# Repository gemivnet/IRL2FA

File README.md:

# IRL2FA

**An air-gapped key fob that proves the person on the other end is who they say they are, and keeps your 2FA codes off your phone.**

AI can now clone a voice from a few seconds of audio and write messages in anyone's style. "It's me, I lost my phone, can you send…" is no longer something you can judge by ear. IRL2FA gives two people a shared secret they set up **once, in person**. From then on, each device shows two words that change every 15 seconds: the word you **say** and the word you should **hear** back. If the reply matches, the other person is holding the device you paired with face to face.

It is also a standard **TOTP authenticator** (the 6-digit codes from Google Authenticator and similar apps) for up to 512 accounts. It has no USB data port, no radio and no network. The only control is a 5-way joystick.

<p align="center">
  <a href="https://irl2fa.com/"><b>▶ Try it in your browser</b></a> ·
  <a href="#build-one">Build one</a> ·
  <a href="docs/pairing-protocol.md">How pairing works</a> ·
  <a href="https://github.com/gemivnet/IRL2FA/releases/latest">Download</a>
</p>

---

## How it works

**Pair once, in person.**

1. Both people choose *Pair with someone* and hold their devices top edge to top edge.
2. The devices agree a 256-bit key over infrared using X25519, with a commitment scheme that stops a man in the middle.
3. Both screens show the same six joystick symbols. You compare them, confirm, and name the contact.

**Verify any time after.**

- Open the contact. Say the **SAY** word; they should answer with your **HEAR** word.
- Words come from HMAC-SHA256 over the current 15-second window, mapped onto the 2048-word BIP-39 list.
- Nothing is ever transmitted again, so there is nothing to intercept.

**TOTP codes.**

- Add an account by typing the base32 secret most sites show under "can't scan the QR code?".
- RFC 6238; SHA1/SHA256/SHA512; 6 or 8 digits; 30 or 60 s.

**Secrets at rest.**

- Every record, labels included, is sealed with XChaCha20-Poly1305 in the MCU's read-protected flash.
- An optional joystick PIN wraps the key with Argon2i. Ten wrong PINs erase the device.

The full design is in [docs/pairing-protocol.md](docs/pairing-protocol.md) and [docs/ui-flows.md](docs/ui-flows.md).

## For family members

Setting one up for a parent, grandparent or child who should only check who is calling? Use **simple mode** (the docs call it vulnerable mode). The device then shows one thing: the name of the person, and in big letters the word that person will say. "If they don't say this word, hang up and call them back." Up and down go to the next person. Nothing else does anything: no menus, no codes, no settings.

1. Pair the device in person with everyone who might call, and give each contact a name they will recognise ("Susan", "Grandpa Joe").
2. **Settings → Simple mode**, then choose a **family PIN** of 6 or more joystick moves and enter it three times. Write it down: it cannot be reset.
3. Give them the device. When you call, open their contact on your own device and say your **SAY** word.

To change anything later, hold the centre of the joystick for 10 seconds and enter the family PIN. Wrong family PINs never erase the device; they make the next try wait longer, up to an hour. Details and the security trade-offs are in [docs/ui-flows.md](docs/ui-flows.md#vulnerable-simple-mode).

## Try the simulator

The firmware's portable core is compiled to WebAssembly and runs two devices side by side in your browser: pair them over a simulated IR link, compare words, add a TOTP secret and check it against your phone.

It behaves like the hardware, not just like the firmware:

- **E-paper.** A full refresh flashes black and white for 3 s; a partial one takes 0.42 s and leaves faint ghosting that builds up until the firmware's next full refresh. Presses during a refresh are queued, as on the board.
- **IR link.** Set the distance and angle between the devices. Bit errors and dropouts rise with distance, and bytes take their real airtime at 4800 baud on a half-duplex link; the firmware listens before it talks. Beyond about 9 cm pairing keeps retrying and gives up after a minute.
- **Battery.** The panel uses the same power model as the [battery budget](docs/power-calculations.md), generated from `hardware/power`. Fast-forward days or years of use and watch the remaining life and the cell voltage fall.

**[irl2fa.com](https://irl2fa.com/)**

## Hardware

| | |
|-|-|
| MCU | STM32U083KCU6: Cortex-M0+, 256 KB flash, 40 KB RAM, TRNG, readout protection |
| Display | 2.13″ e-paper, 250×122, Good Display GDEY0213B74 (SSD1680) |
| Clock | Micro Crystal RV-3032-C7, temperature-compensated ±2.5 ppm |
| Input | Alps SKRHABE010 5-way switch, the only control |
| Pairing | 940 nm side-looking IR LED and phototransistor on the top edge |
| Power | CR2450 coin cell. **About 2.8 years typical, 1.6 years worst case** at 20 uses a day, with the awake time and refreshes measured on the emulated firmware ([calculation](docs/power-calculations.md)) |
| Board | 77 × 31 mm, 2 layers, 0.8 mm, ENIG. JLCPCB can assemble every part except the display |
| Case | 80.9 × 34.9 × 11.0 mm, 3D-printed in 4 parts, M2 screws |

- Design files: [schematic (PDF)](hardware/fab/irl2fa-schematic.pdf) · [KiCad 9 project](hardware/) · [interactive BOM](https://irl2fa.com/ibom.html) · [3D model (STEP)](hardware/fab/irl2fa.step)
- Design notes: [PCB design](docs/pcb-design.md) · [pin assignments](docs/pin-assignments.md) · [why these parts](docs/hardware-options.md) · [design review](docs/design-review.md) · [firmware against the silicon](docs/firmware-hardware-review.md)

## Build one

You need a PCB, a display, a coin cell, a printed case and four screws. Everything to order is committed and kept current by CI.

1. **Order the assembled board** from [JLCPCB](https://jlcpcb.com). The form has a few answers that would spoil the boards; [docs/assembly-review.md](docs/assembly-review.md#ordering-at-jlcpcb) explains each one.
   - Upload [`hardware/fab/irl2fa-gerbers.zip`](hardware/fab/irl2fa-gerbers.zip) and keep the detected size (77 × 31 mm) and 2 layers.
   - **Delivery format: Panel by JLCPCB**, 1 column × 2 rows, with **edge rails** on the long sides, joined by **stamp holes (mouse bites), not V-cut**. Assembling both sides needs Standard PCBA, which only takes boards or panels of at least 70 × 70 mm.
   - **PCB thickness 0.8 mm**, **surface finish ENIG** (a bare pad is the coin cell's negative contact), **via covering Tented**, 1 oz copper, any colour.
   - **Remove order number: Yes**: the board has no spot reserved for it.
   - Turn on **PCB Assembly**: **PCBA type Standard**, **assembly side Both sides** (the joystick is on the front, everything else on the back), **tooling holes added by JLCPCB**, **Confirm Parts Placement: Yes**.
   - Add [`irl2fa-bom-jlcpcb.csv`](hardware/fab/irl2fa-bom-jlcpcb.csv) and [`irl2fa-cpl-jlcpcb.csv`](hardware/fab/irl2fa-cpl-jlcpcb.csv). Every part has an LCSC number. The [BOM](docs/bill-of-materials.md) lists JLCPCB's stock, Basic/Extended parts and alternatives. The MCU and the RTC are often short, so check them before paying.
   - The placement file is already corrected for JLCPCB's own footprints. On the placement preview, check the polarised parts against the [expected-view table](docs/assembly-review.md#what-the-placement-preview-must-show), especially the IR LED and phototransistor (lenses at the top edge) and the coin-cell clip (open end at the bottom edge).
   - Paste the [order remark](docs/assembly-review.md#order-remark) into the remark box.
   - **Optional: have JLCPCB flash the firmware.** In the Standard PCBA options, open the advanced options and choose **programming**. JLCPCB asks for:
     - the MCU: **STM32U083KCU6**;
     - the programming interface: SWD on five test pads on the back, along the bottom edge, 1.5 mm round on a 2.54 mm grid: **TP2 GND, TP1 VBAT (supply 3.0 V), TP3 SWDIO, TP4 SWCLK, TP5 NRST**. Positions and a board image are in [docs/pcb-design.md](docs/pcb-design.md#factory-programming); attach [`docs/images/pcb/pcb-back.png`](docs/images/pcb/pcb-back.png);
     - the firmware: the factory image `irl2fa-factory-<version>.bin` from the [latest release](https://github.com/gemivnet/IRL2FA/releases) (bootloader + signed firmware in one file), written from the start of flash (0x08000000). Do not send the application's `.elf` alone: it does not start without the bootloader. The chip is left unprotected; readout protection is only ever turned on by its owner, from Settings.

     It costs about $8 in engineering fees plus operator time per board. JLCPCB decides per order whether it can program a part, so the option can be refused. A freshly programmed chip runs ST's bootloader, not the firmware, until it has seen a power-on reset ([firmware review](docs/firmware-hardware-review.md) F4): the board must be power-cycled after the first flash. Inserting the coin cell does that; a board that is checked still on the fixture after programming looks dead, and is not.
   - To solder it yourself, use the [interactive BOM](https://irl2fa.com/ibom.html).
2. **Buy the display.** A [Good Display GDEY0213B74](https://www.good-display.com/product/391.html) (about $5), or the GDEM0213B74WT if it has to work below 0 °C.
3. **Print the case.**
   - Files: [`case/stl/`](case/stl/) or [`case/3mf/irl2fa-all.3mf`](case/3mf/), in PETG or PLA with no supports.
   - Settings and assembly: [docs/case-design.md](docs/case-design.md).
4. **Flash the firmware.**
   - Get the factory image `irl2fa-factory-<version>.hex` (bootloader + signed firmware, for the whole chip) from the [latest release](https://github.com/gemivnet/IRL2FA/releases), or build `firmware/build/stm32u0/irl2fa-factory.hex` with `firmware/port/stm32u0/build.sh` (unsigned: a development unit).
   - Flash it through a Tag-Connect TC2030-NL cable and any ST-Link: [firmware/port/stm32u0/README.md](firmware/port/stm32u0/README.md). The test pads TP1-TP5 on the back carry the same signals for a pogo-pin fixture or probe clips. Skip this step if JLCPCB programmed the boards.
   - The chip stays unprotected (anyone with a debug cable could read it) until you choose **Settings → Lock debug port** on a fresh cell. Do that once the device is set up; it is permanent unless the chip is erased, and updates over IR still work ([details](docs/firmware-updates.md#locking-the-debug-port)).
   - Later versions go on over infrared, no cable: see [Updating](#updating).
5. **Assemble.**
   - Thread the display's flex cable through the slot from the front and lock it into the connector on the back (J1), then stick the display down on the front. Done the other way round, the flex has to be bent back over the glass at its glued root to reach the slot.
   - Slide the CR2450 under its clip from the bottom edge and screw the case together. Flash first (step 4): the Tag-Connect pads are on the back, inside the case.
   - Set the time: the device asks on first start.

Built one? Please [file a build report](https://github.com/gemivnet/IRL2FA/issues/new?template=build_report.yml).

> **Status:** v0.2 is a complete, simulated and checked design, but no board has been built yet. The first boards will confirm the panel orientation, the IR range and the real sleep current. Until a build report says otherwise, treat it as a prototype.

## Updating

New firmware goes on over infrared, from another IRL2FA or from a computer
with a ~$5 USB infrared adapter. Settings → Firmware update → Receive an
update (with the PIN, if set), then send the release's `.irl2fa` file:

```sh
python3 firmware/tools/irl2fa_update.py --port /dev/ttyUSB0 irl2fa-v0.2.0.irl2fa
```

or, from a device that already runs it, Settings → Firmware update → Send it
to another. About two minutes. Codes, contacts and settings stay. The
bootloader accepts only firmware signed with the IRL2FA release key, never an
older version, and a cell pulled at any moment leaves a device that starts.
Details, the adapter, and the security model: [docs/firmware-updates.md](docs/firmware-updates.md).

## Every change is simulated

The hardware is open to modification, and people order straight from this repository. So every push runs:

- ERC and DRC (with schematic parity and silkscreen checks as errors), and the IR parts facing out through the top edge
- every footprint checked against its manufacturer's land-pattern drawing, and its pins against the schematic
- netlist checks against the pin map shared with the firmware
- SPICE simulations of the coin cell, e-paper booster, power switch, reverse-battery protection and IR driver
- the battery-life budget, with the on-times measured by running the real firmware through a scripted use and a pairing in the emulator
- a check that the committed Gerbers, BOM and placement files match the KiCad files
- Gerber sanity checks
- case-fit tests
- firmware unit tests (RFC test vectors) and UI flows, with a coverage minimum
- a power cut after every flash operation of every store write, which must leave the old state or the new one
- fuzzing of the IR parser, pairing, the encrypted store, base32 input and the whole app
- constant-time checks of PIN verification, MAC compares and the pairing crypto
- static analysis (cppcheck, clang-tidy) with zero findings
- a formal model of the pairing protocol (Tamarin): the key stays secret and a man in the middle has to commit before he sees an honest key
- the real firmware binary running on an emulated STM32 (Renode), where two virtual devices pair

Details: [docs/hardware-testing.md](docs/hardware-testing.md).

```sh
make check   # everything CI runs, locally (needs Docker)
```

## Repository layout

```
firmware/core/          portable C11: crypto, TOTP, words, pairing, encrypted store, UI
firmware/port/stm32u0/  the device: HAL, SSD1680 and RV-3032 drivers, startup, linker script
firmware/renode/        emulated STM32U083 + peripheral models + Robot tests
firmware/tests/         host unit tests
sim/                    the browser simulator (WebAssembly)
hardware/               KiCad 9 project, pins.yaml, board.yaml, SPICE benches, power model, fab outputs
hardware/lib/           footprints, symbols and 3D models (drawn from datasheets)
case/                   OpenSCAD case, STL/3MF exports, fit tests
docs/                   design documents and images
```

## Why this exists

The original idea (2025): a pocket device that does one thing well, proving that a familiar voice or a familiar account is really the person you know. It has no app, no cloud and no battery to charge every night. The 2026 restart rebuilt the design around what that needs to be safe in practice: a full-strength key exchange instead of a typed code, secrets that never leave the chip, and enough tests that strangers can change it with confidence. See [docs/design-review.md](docs/design-review.md).

**Security notes.**

- A verification word proves possession of a paired device and a clock within about 15 s, nothing more.
- Someone holding your unlocked device can answer for you, which is what the PIN is for.
- Keep the device's clock right: TOTP needs it within about 30 s, and the RTC drifts at most about 80 s a year.
- Report vulnerabilities privately via the Security tab.

## Contributing

Contributions are welcome: firmware, hardware, case, docs, translations of the wordlist. Read [CONTRIBUTING.md](CONTRIBUTING.md) first: `main` must always be orderable, and CI enforces it.

## License

| Part | Licence |
|-|-|
| Firmware and simulator | [AGPL-3.0-or-later](LICENSE) |
| Hardware (schematic, PCB, footprints, models) | [CERN-OHL-S-2.0](hardware/LICENSE) |
| Case | [CC-BY-SA-4.0](case/LICENSE) |

You may use, modify, build and sell all of it, as long as derivatives stay open under the same terms. Third-party components are listed in [THIRD_PARTY.md](THIRD_PARTY.md).

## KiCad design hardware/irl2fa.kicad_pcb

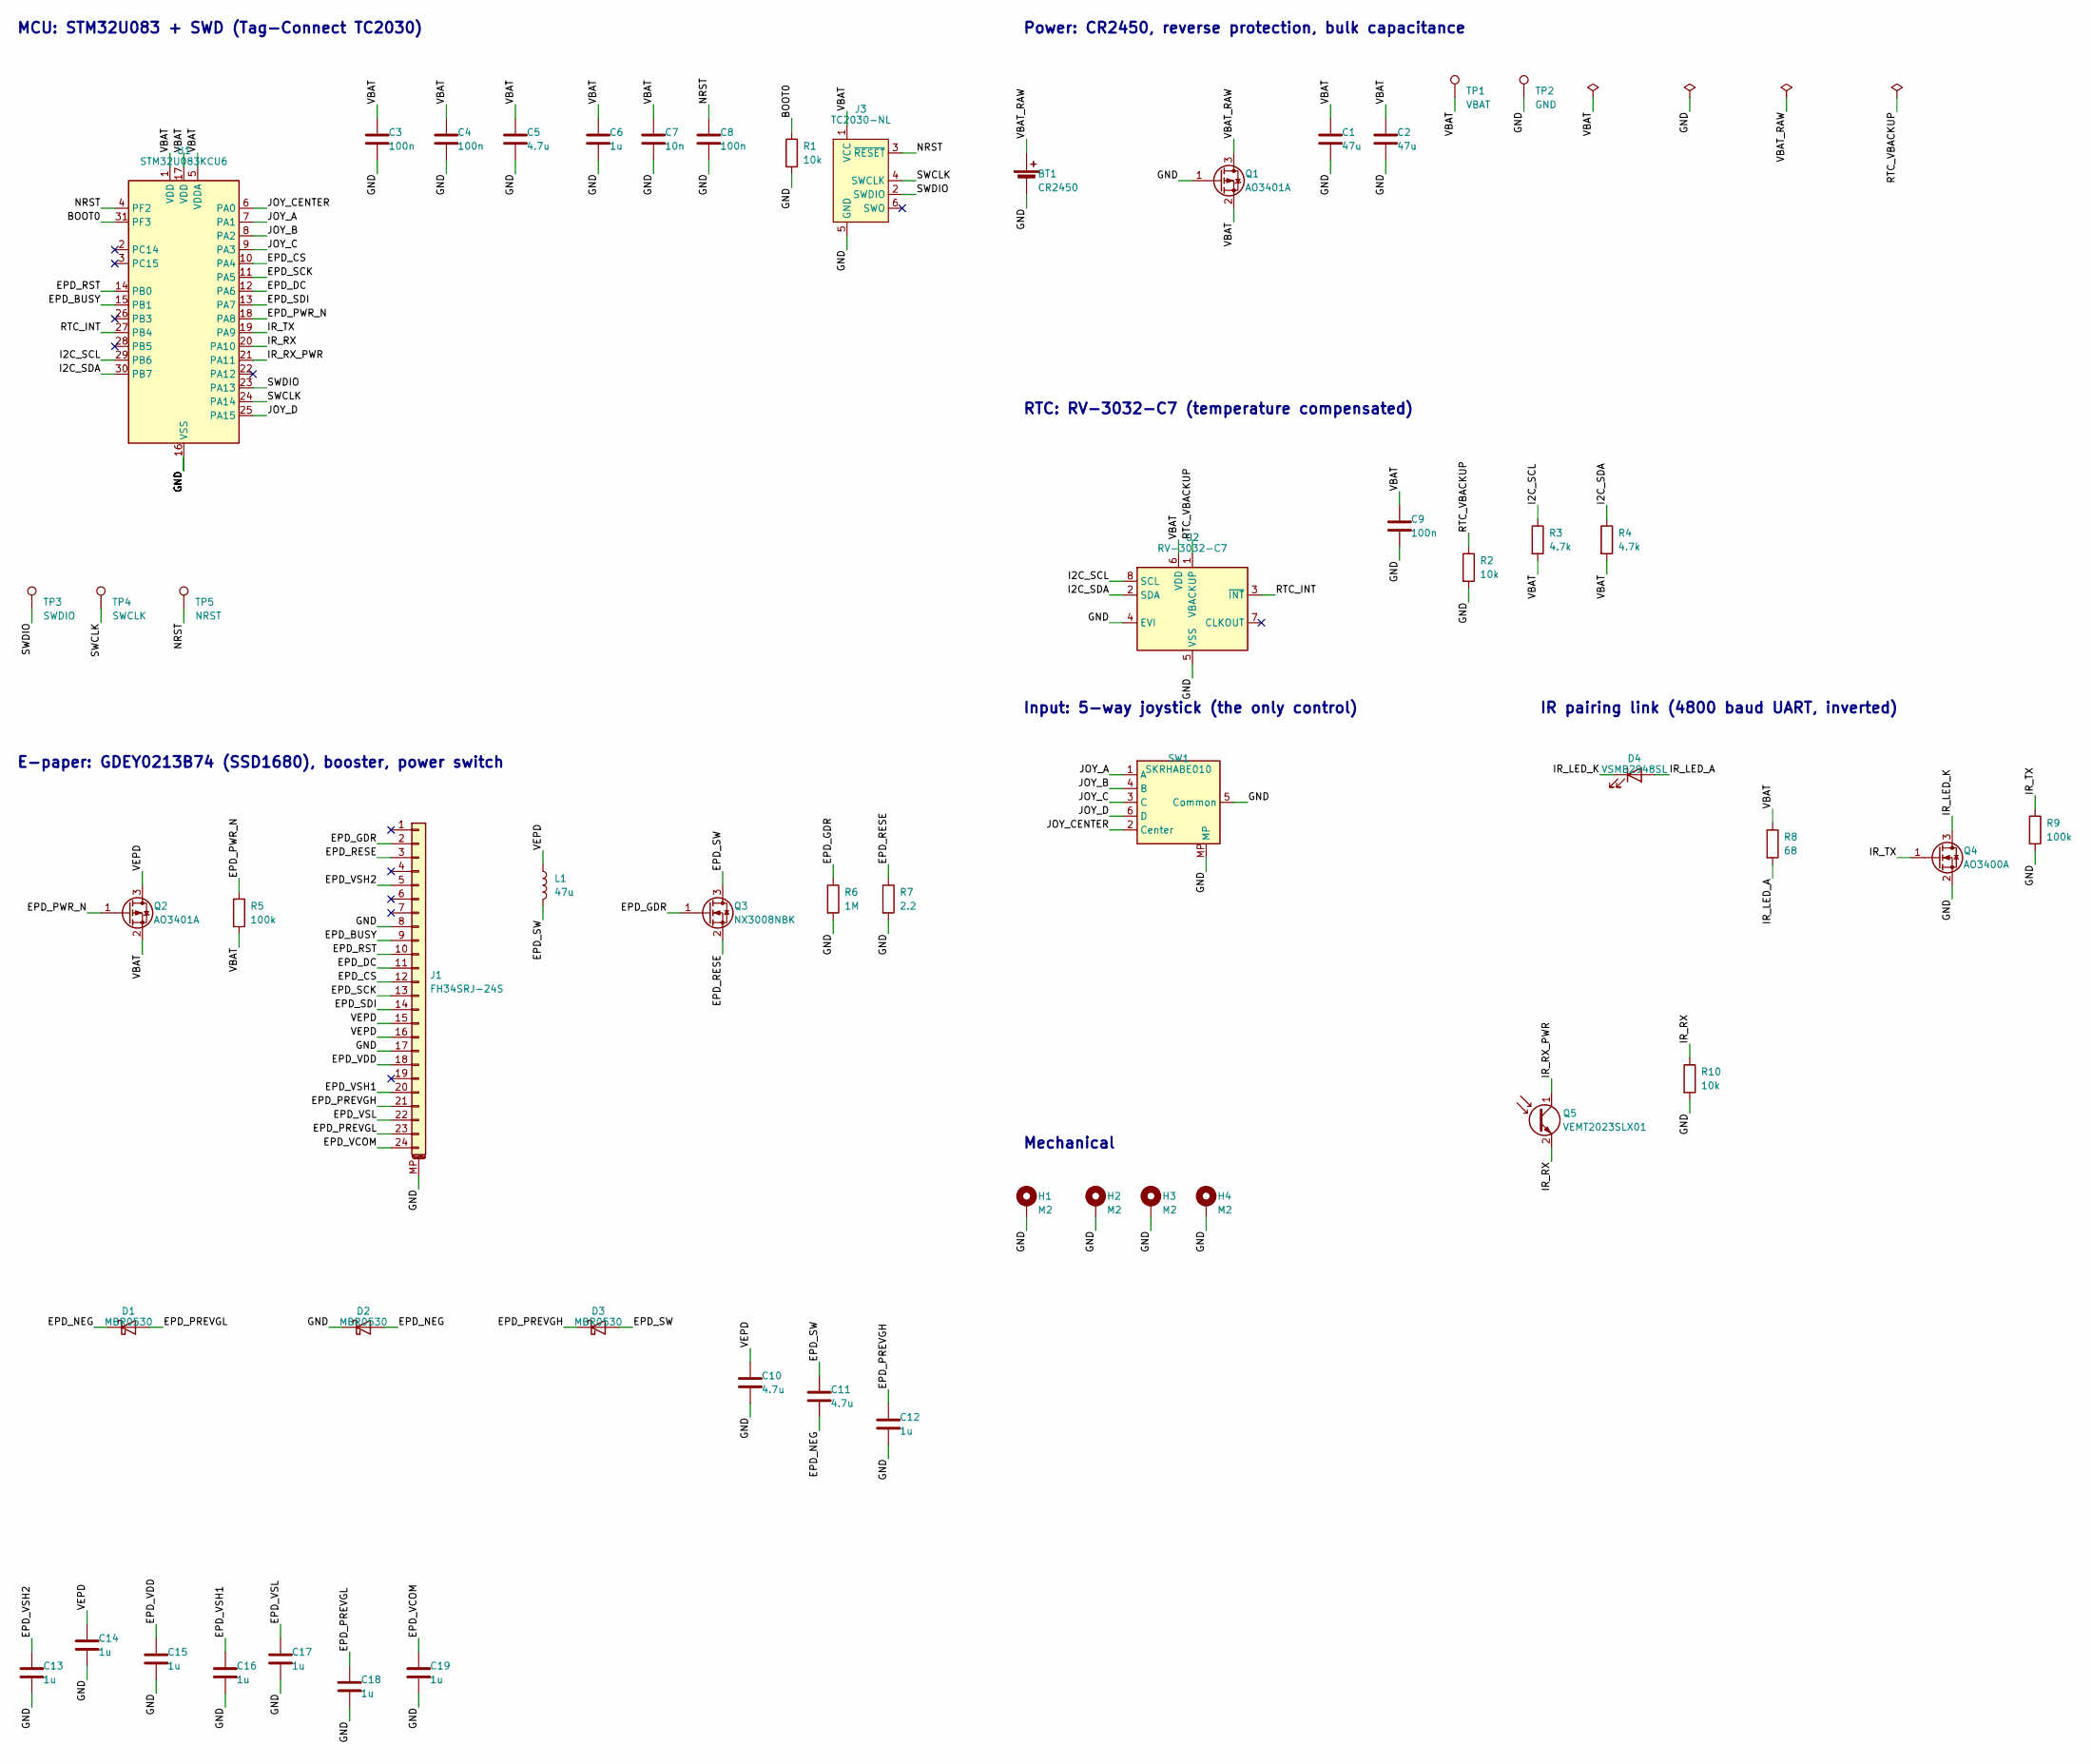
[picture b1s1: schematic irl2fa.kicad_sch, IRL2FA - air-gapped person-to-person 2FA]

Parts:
BT1: CR2450; BatteryHolder_MYOUNG_MY-2450-01_CR2450; MPN MY-2450-01; LCSC C964845
C1, C2: 47u; C_0805_2012Metric; MPN CL21A476MQYNNNE; LCSC C16780
C3, C4, C8, C9: 100n; C_0402_1005Metric; MPN CL05B104KO5NNNC; LCSC C1525
C5: 4.7u; C_0603_1608Metric; MPN CL10A475KO8NNNC; LCSC C19666
C6: 1u; C_0402_1005Metric; MPN CL05A105KA5NQNC; LCSC C52923
C7: 10n; C_0402_1005Metric; MPN CL05B103KB5NNNC; LCSC C15195
C10, C11: 4.7u; C_0805_2012Metric; MPN CL21A475KAQNNNE; LCSC C1779
C12, C13, C14, C15, C16, C17, C18, C19: 1u; C_0603_1608Metric; MPN CL10A105KB8NNNC; LCSC C15849
D1, D2, D3: MBR0530; D_SOD-123; MPN MBR0530; LCSC C77336
D4: VSMB2948SL; LED_Vishay_VSMB2948SL_SideView; MPN VSMB2948SL; LCSC C6604342
H1, H2, H3, H4: M2; MountingHole_2.2mm_M2_Pad
J1: FH34SRJ-24S; Hirose_FH34SRJ-24S-0.5SH_1x24-1MP_P0.50mm_Horizontal; MPN FH34SRJ-24S-0.5SH(50); LCSC C324726
J3: TC2030-NL; Tag-Connect_TC2030-IDC-NL_2x03_P1.27mm_Vertical
L1: 47u; L_APV_ANR3015; MPN ANR3015T470M; LCSC C7427088
Q1, Q2: AO3401A; SOT-23; MPN AO3401A; LCSC C15127
Q3: NX3008NBK; SOT-23; MPN NX3008NBK,215; LCSC C179399
Q4: AO3400A; SOT-23; MPN AO3400A; LCSC C20917
Q5: VEMT2023SLX01; PhotoTransistor_Vishay_VEMT2023SLX01_SideView; MPN VEMT2023SLX01; LCSC C2843576
R1, R2, R10: 10k; R_0402_1005Metric; MPN 0402WGF1002TCE; LCSC C25744
R3, R4: 4.7k; R_0402_1005Metric; MPN 0402WGF4701TCE; LCSC C25900
R5, R9: 100k; R_0402_1005Metric; MPN 0402WGF1003TCE; LCSC C25741
R6: 1M; R_0402_1005Metric; MPN 0402WGF1004TCE; LCSC C26083
R7: 2.2; R_0402_1005Metric; MPN 0402WGF220KTCE; LCSC C25101
R8: 68; R_0402_1005Metric; MPN 0402WGF680JTCE; LCSC C25131
SW1: SKRHABE010; SW_Nav_Alps_SKRHABE010; MPN SKRHABE010; LCSC C139794
TP1: VBAT; TestPoint_Pad_D1.5mm
TP2: GND; TestPoint_Pad_D1.5mm
TP3: SWDIO; TestPoint_Pad_D1.5mm
TP4: SWCLK; TestPoint_Pad_D1.5mm
TP5: NRST; TestPoint_Pad_D1.5mm
U1: STM32U083KCU6; UFQFPN-32-1EP_5x5mm_P0.5mm_EP3.5x3.5mm; MPN STM32U083KCU6; LCSC C22459164
U2: RV-3032-C7; MicroCrystal_C7_SON-8_1.5x3.2mm_P0.9mm; MPN RV-3032-C7 32.768kHz 2.5ppm-TA-QC; LCSC C5127802

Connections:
/BOOT0: R1.1, U1.31 (PF3)
/EPD_BUSY: J1.9, U1.15 (PB1)
/EPD_CS: J1.12, U1.10 (PA4)
/EPD_DC: J1.11, U1.12 (PA6)
/EPD_GDR: J1.2, Q3.1 (G), R6.1
/EPD_NEG: C11.2, D1.1 (K), D2.2 (A)
/EPD_PREVGH: C12.1, D3.1 (K), J1.21
/EPD_PREVGL: C18.1, D1.2 (A), J1.23
/EPD_PWR_N: Q2.1 (G), R5.1, U1.18 (PA8)
/EPD_RESE: J1.3, Q3.2 (S), R7.1
/EPD_RST: J1.10, U1.14 (PB0)
/EPD_SCK: J1.13, U1.11 (PA5)
/EPD_SDI: J1.14, U1.13 (PA7)
/EPD_SW: C11.1, D3.2 (A), L1.2, Q3.3 (D)
/EPD_VCOM: C19.1, J1.24
/EPD_VDD: C15.1, J1.18
/EPD_VSH1: C16.1, J1.20
/EPD_VSH2: C13.1, J1.5
/EPD_VSL: C17.1, J1.22
/GND: BT1.2 (-), C1.2, C2.2, C3.2, C4.2, C5.2, C6.2, C7.2, C8.2, C9.2, C10.2, C12.2, C13.2, C14.2, C15.2, C16.2, C17.2, C18.2, C19.2, D2.1 (K), H1.1, H2.1, H3.1, H4.1, J1.8, J1.17, J1.MP (MountPin), J3.5 (GND), Q1.1 (G), Q4.2 (S), R1.2, R2.2, R6.2, R7.2, R9.2, R10.2, SW1.5 (Common), SW1.MP, TP2.1, U1.16 (VSS), U1.32 (VSS), U1.33 (VSS), U2.4 (EVI), U2.5 (VSS)
/I2C_SCL: R3.1, U1.29 (PB6), U2.8 (SCL)
/I2C_SDA: R4.1, U1.30 (PB7), U2.2 (SDA)
/IR_LED_A: D4.2 (A), R8.2
/IR_LED_K: D4.1 (K), Q4.3 (D)
/IR_RX: Q5.2 (E), R10.1, U1.20 (PA10)
/IR_RX_PWR: Q5.1 (C), U1.21 (PA11)
/IR_TX: Q4.1 (G), R9.1, U1.19 (PA9)
/JOY_A: SW1.1 (A), U1.7 (PA1)
/JOY_B: SW1.4 (B), U1.8 (PA2)
/JOY_C: SW1.3 (C), U1.9 (PA3)
/JOY_CENTER: SW1.2 (Center), U1.6 (PA0)
/JOY_D: SW1.6 (D), U1.25 (PA15)
/NRST: C8.1, J3.3 (~RESET), TP5.1, U1.4 (PF2)
/RTC_INT: U1.27 (PB4), U2.3 (~INT)
/RTC_VBACKUP: R2.1, U2.1 (VBACKUP)
/SWCLK: J3.4 (SWCLK), TP4.1, U1.24 (PA14)
/SWDIO: J3.2 (SWDIO), TP3.1, U1.23 (PA13)
/VBAT: C1.1, C2.1, C3.1, C4.1, C5.1, C6.1, C7.1, C9.1, J3.1 (VCC), Q1.2 (S), Q2.2 (S), R3.2, R4.2, R5.2, R8.1, TP1.1, U1.1 (VDD), U1.5 (VDDA), U1.17 (VDD), U2.6 (VDD)
/VBAT_RAW: BT1.1 (+), Q1.3 (D)
/VEPD: C10.1, C14.1, J1.15, J1.16, L1.1, Q2.3 (D)

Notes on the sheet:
Power: CR2450, reverse protection, bulk capacitance
MCU: STM32U083 + SWD (Tag-Connect TC2030)
RTC: RV-3032-C7 (temperature compensated)
Input: 5-way joystick (the only control)
E-paper: GDEY0213B74 (SSD1680), booster, power switch
IR pairing link (4800 baud UART, inverted)
Mechanical

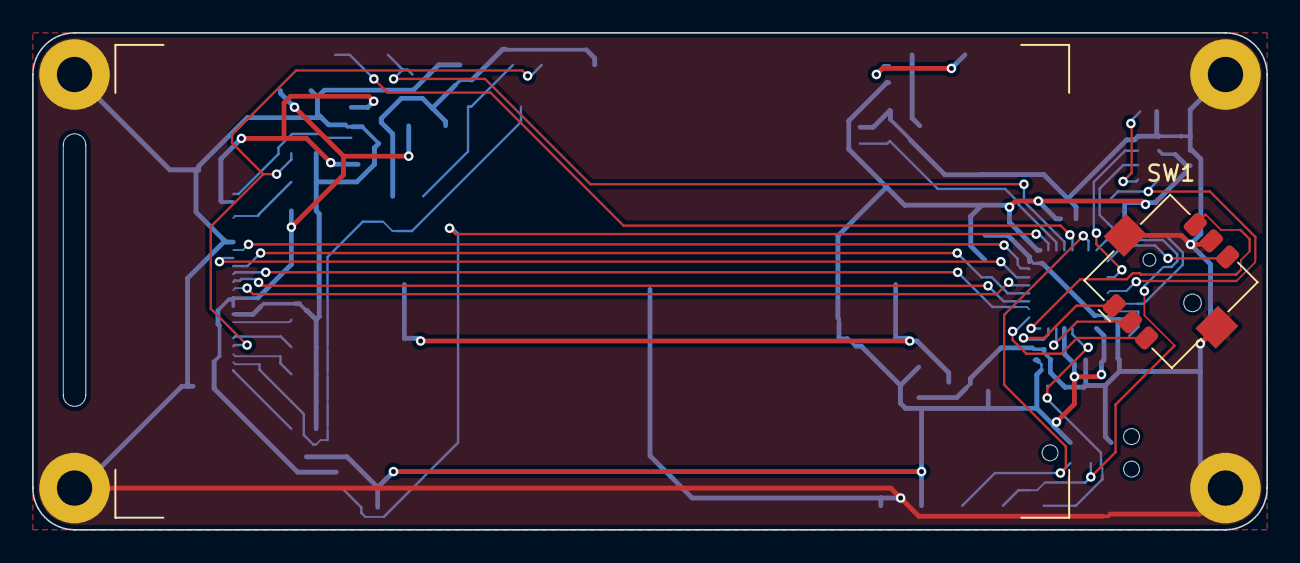
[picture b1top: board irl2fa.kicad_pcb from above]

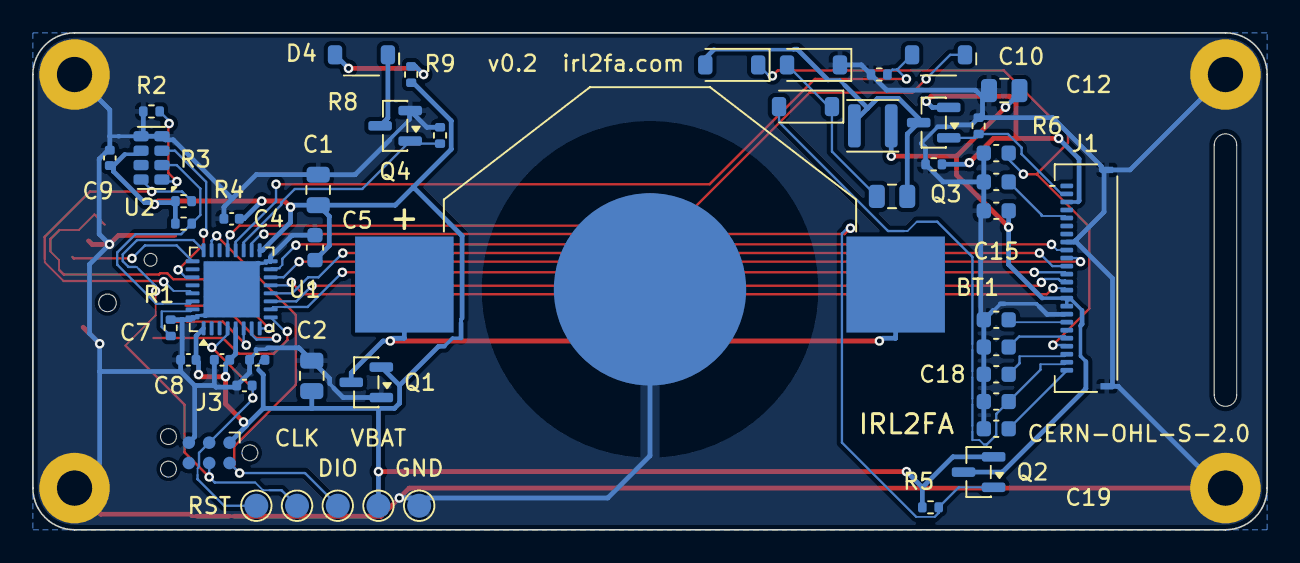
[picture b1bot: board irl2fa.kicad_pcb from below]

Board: 2 copper layers, 77.0 x 31.0 mm, 55 parts (49 on the bottom side), 40 nets.

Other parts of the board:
DS1: GDEY0213B74; EPD_GoodDisplay_GDEY0213B74_Outline

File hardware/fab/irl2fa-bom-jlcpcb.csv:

Comment,Designator,Footprint,LCSC Part #
CR2450,BT1,BatteryHolder_MYOUNG_MY-2450-01_CR2450,C964845
47u,"C1,C2",C_0805_2012Metric,C16780
100n,"C3,C4,C8,C9",C_0402_1005Metric,C1525
4.7u,C5,C_0603_1608Metric,C19666
1u,C6,C_0402_1005Metric,C52923
10n,C7,C_0402_1005Metric,C15195
4.7u,"C10,C11",C_0805_2012Metric,C1779
1u,"C12,C13,C14,C15,C16,C17,C18,C19",C_0603_1608Metric,C15849
MBR0530,"D1,D2,D3",D_SOD-123,C77336
VSMB2948SL,D4,LED_Vishay_VSMB2948SL_SideView,C6604342
FH34SRJ-24S,J1,Hirose_FH34SRJ-24S-0.5SH_1x24-1MP_P0.50mm_Horizontal,C324726
47u,L1,L_APV_ANR3015,C7427088
AO3401A,"Q1,Q2",SOT-23,C15127
NX3008NBK,Q3,SOT-23,C179399
AO3400A,Q4,SOT-23,C20917
VEMT2023SLX01,Q5,PhotoTransistor_Vishay_VEMT2023SLX01_SideView,C2843576
10k,"R1,R2,R10",R_0402_1005Metric,C25744
4.7k,"R3,R4",R_0402_1005Metric,C25900
100k,"R5,R9",R_0402_1005Metric,C25741
1M,R6,R_0402_1005Metric,C26083
2.2,R7,R_0402_1005Metric,C25101
68,R8,R_0402_1005Metric,C25131
SKRHABE010,SW1,SW_Nav_Alps_SKRHABE010,C139794
STM32U083KCU6,U1,UFQFPN-32-1EP_5x5mm_P0.5mm_EP3.5x3.5mm,C22459164
RV-3032-C7,U2,MicroCrystal_C7_SON-8_1.5x3.2mm_P0.9mm,C5127802

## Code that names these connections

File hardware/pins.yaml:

# STM32U083KCU6 (UFQFPN32) pin assignment: the single source of truth.
#
#   firmware/port/stm32u0/pins.h  is generated from this file (hardware/tools/gen_pins.py)
#   hardware/tests/test_netlist.py checks the schematic netlist against it
#   docs/pin-assignments.md       is generated from it
#
# pin: package pin number; net: schematic net name; af: alternate function
# number (null = GPIO); notes are copied into the docs.
# SPDX-License-Identifier: CERN-OHL-S-2.0
mcu: STM32U083KCU6
package: UFQFPN32
pins:
  - {pin: 1,  name: VDD,   net: VBAT}
  - {pin: 2,  name: PC14,  net: null,        notes: "spare (LSE pins unused; RTC is external)"}
  - {pin: 3,  name: PC15,  net: null,        notes: spare}
  - {pin: 4,  name: PF2,   net: NRST,        notes: "NRST, 100 nF to GND, Tag-Connect J3, test pad TP5"}
  - {pin: 5,  name: VDDA,  net: VBAT,        notes: "battery voltage measured via VREFINT"}
  - {pin: 6,  name: PA0,   net: JOY_CENTER,  mode: input_pullup, exti: true, symbol: JOY_CENTER, notes: "joystick push (WKUP1)"}
  - {pin: 7,  name: PA1,   net: JOY_A,       mode: input_pullup, exti: true, symbol: JOY_A, notes: "joystick direction A"}
  - {pin: 8,  name: PA2,   net: JOY_B,       mode: input_pullup, exti: true, symbol: JOY_B, notes: "joystick direction B"}
  - {pin: 9,  name: PA3,   net: JOY_C,       mode: input_pullup, exti: true, symbol: JOY_C, notes: "joystick direction C"}
  - {pin: 10, name: PA4,   net: EPD_CS,      mode: output, symbol: EPD_CS, notes: "e-paper chip select (GPIO)"}
  - {pin: 11, name: PA5,   net: EPD_SCK,     mode: af, af: 5, symbol: EPD_SCK, notes: SPI1_SCK}
  - {pin: 12, name: PA6,   net: EPD_DC,      mode: output, symbol: EPD_DC, notes: "e-paper data/command"}
  - {pin: 13, name: PA7,   net: EPD_SDI,     mode: af, af: 5, symbol: EPD_SDI, notes: SPI1_MOSI}
  - {pin: 14, name: PB0,   net: EPD_RST,     mode: output, symbol: EPD_RST, notes: "e-paper reset, active low"}
  - {pin: 15, name: PB1,   net: EPD_BUSY,    mode: input, symbol: EPD_BUSY, notes: "e-paper busy, high = busy (SSD1680)"}
  - {pin: 16, name: VSS,   net: GND}
  - {pin: 17, name: VDD,   net: VBAT,        notes: "VDD/VDDUSB, own 100 nF"}
  - {pin: 18, name: PA8,   net: EPD_PWR_N,   mode: output, symbol: EPD_PWR_N, notes: "e-paper load switch, low = on"}
  - {pin: 19, name: PA9,   net: IR_TX,       mode: af, af: 7, symbol: IR_TX, notes: "USART1_TX, inverted (idle = LED off)"}
  - {pin: 20, name: PA10,  net: IR_RX,       mode: af, af: 7, symbol: IR_RX, notes: "USART1_RX, inverted"}
  - {pin: 21, name: PA11,  net: IR_RX_PWR,   mode: output, symbol: IR_RX_PWR, notes: "powers the phototransistor"}
  - {pin: 22, name: PA12,  net: null,        notes: spare}
  - {pin: 23, name: PA13,  net: SWDIO,       mode: af, af: 0, notes: "SWD, Tag-Connect J3, test pad TP3"}
  - {pin: 24, name: PA14,  net: SWCLK,       mode: af, af: 0, notes: "SWD, Tag-Connect J3, test pad TP4"}
  - {pin: 25, name: PA15,  net: JOY_D,       mode: input_pullup, exti: true, symbol: JOY_D, notes: "joystick direction D"}
  - {pin: 26, name: PB3,   net: null,        notes: spare}
  - {pin: 27, name: PB4,   net: RTC_INT,     mode: input_pullup, exti: true, symbol: RTC_INT, notes: "RV-3032 INT, open drain"}
  - {pin: 28, name: PB5,   net: null,        notes: spare}
  - {pin: 29, name: PB6,   net: I2C_SCL,     mode: af, af: 4, symbol: I2C_SCL, notes: "I2C1_SCL, 4.7k pull-up"}
  - {pin: 30, name: PB7,   net: I2C_SDA,     mode: af, af: 4, symbol: I2C_SDA, notes: "I2C1_SDA, 4.7k pull-up"}
  - {pin: 31, name: PF3,   net: BOOT0,       notes: "BOOT0, 10k pull-down"}
  - {pin: 32, name: VSS,   net: GND}
  - {pin: 33, name: EP,    net: GND,         notes: "exposed pad"}

# Joystick: in the Alps SKRH footprint the four contacts sit at the body's
# corners (A top-left, B top-right, C bottom-left, D bottom-right; A/D and B/C
# are opposite). The footprint is rotated +45 degrees on the board, which
# turns them into left/up/down/right as seen from the front with the screen
# upright:
joystick:
  JOY_A: left
  JOY_B: up
  JOY_C: down
  JOY_D: right
  JOY_CENTER: center

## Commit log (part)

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2024-11-20 add initial readme
2024-11-20 add license
2024-11-20 add contributing guidelines
2024-11-20 update contributing guide
2024-11-20 update readme to remove contributions
2025-01-28 configure project structure, start adding components, add docs
2025-01-28 reorganize folders

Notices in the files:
README.md:
License: AGPL-3.0 | CERN-OHL-S-2.0 | CC-BY-SA-4.0
hardware/irl2fa.kicad_sch:
Licence: CERN-OHL-S-2.0
